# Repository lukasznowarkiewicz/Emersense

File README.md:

# Emersense - Emergency Vehicle Detection System

## Introduction

Emersense is an innovative project developed by a group of dedicated students from Poznan University of Technology. Initiated during the challenging times of the pandemic, this project was brought to life entirely remotely by a team of four members located in four different cities across Poland. The project was realized as part of a competition organized by Enactus Poland, within the framework of the Enactus student organization, which promotes socially responsible projects.

The primary issue that Emersense aims to address is the often too-late response to an approaching emergency vehicle. This problem poses a significant risk not only to the efficiency of emergency services but also to the safety of both the emergency responders and the general public. By leveraging advanced technology, Emersense seeks to provide a timely warning about approaching emergency vehicles, thereby improving response times and reducing the potential for accidents.

## Solution Overview

The core of the Emersense project is a device that uses microphone data to detect emergency vehicle sirens amidst urban noise. It distinguishes these sirens from other sounds such as street noise and engine sounds, and informs the driver of their presence.

- **Siren Detection:** Utilizes signal processing to identify emergency vehicle sirens.
- **Driver Alert:** Notifies the driver through auditory and visual signals.

## Initial Trials on a PC

At the start, we gathered lots of different siren sounds from the internet to build a sound database for Emersense. We quickly found out there's a huge variety of siren sounds. These sounds not only change from one emergency vehicle to another but also differ a lot between countries. There wasn’t even a standard for sirens within the EU. Despite these challenges, we began with the easiest siren sounds to recognize: the sweep and two-tone sirens.

Our first try at figuring out the siren sounds used the FFT (Fast Fourier Transform) library on a computer with an 8-core Intel Core i7 processor. But, we soon realized it was too complex to process the sounds in real time on this setup. So, we switched to the DFT (Discrete Fourier Transform), which was faster and allowed us to make our first successful programs that could recognize two-tone sirens.

Knowing we couldn’t use Python code directly on a microcontroller for the final product, we started to look into low-power hardware that could work for the Emersense device. This was a big step because it helped us focus on finding a solution that could actually be built into a real, working device.

## Trials on the DevKit

After our initial success, we started writing similar code in C for the ESP32 microcontroller. Our first goal was to get a correct spectrum of the signal received from the microphone. 

We soon realized that an electret microphone with an operational amplifier connected to an analog input was giving very inconsistent results. After trying out three more microphone modules, which all produced similarly poor outcomes, we switched to a MEMS microphone that uses the I2S bus - the INMP441. 

Eventually, we managed to get preliminarily satisfying results and programmed it to recognize one type of two-tone siren.

https://github.com/lukasznowarkiewicz/Emersense/assets/82212257/3abe5127-96e8-427c-9536-c156f4cf9e74

## Device on a Custom PCB

As the project evolved, it became necessary for the device not only to function efficiently but also to have an appealing marketing appearance. This required moving away from the mess of wires on breadboards and prototype boards and towards giving the device a sensible shape on a custom PCB, along with a fitting enclosure.

### PCB Design

- **Software:** The PCB was designed in KiCad 5.
- **Components:**
  - **ESP32 Module:** Core processing unit.
  - **CP2102N:** For USB connectivity, allowing programming and data reading through the console.
  - **XL1509:** A converter for stepping down from 5V to 3.3V.
  - **SI4713 FM Transmitter with RDS:** We planned to generate an 'Traffic' RDS signal, which could switch nearby car radios to a traffic channel to broadcast information about the approaching emergency vehicle.
  - **MPU-6050:** For activating energy-saving mode when the vehicle is stationary for an extended period.
  - **INMP441 Digital Microphone and a Legacy Electret Microphone with Amplifier:** To test if the PCB, without the mess of wires, would collect fewer interferences.
  - **SPI 1.3 inch LCD Display (240x240 pixels) with ST7789s Controller.**
- **Shape and Assembly:** The PCB was designed in a round form to accommodate two versions of the device. It was ordered from JLCPCB, with parts from LCSC and manually assembled using a hand-operated pick and place machine.

https://github.com/lukasznowarkiewicz/Emersense/assets/82212257/2ed6d327-44b5-4cf7-a69e-9ff8332732e1

### Enclosure Design

- **Software:** Designed in Fusion 360.
- **Versions:** Two variants were created - one to be mounted on the windshield and another to be inserted into the cigarette lighter socket.
- **Manufacturing:** The enclosures were printed on an Anycubic Photon S SLA printer and cured under a UV nail lamp for hardening.

This stage marked a significant advancement towards finalizing the product, focusing on both functionality and aesthetics.

## Testing and Further Work

This phase was particularly challenging. We were focused on improving the software, but progress was slow. Even with relatively simple sirens, it was difficult to balance the system's sensitivity to quickly detect sirens without being triggered by random noises. More accurate methods, like the autocorrelation function between the spectrum of a reference signal and the captured signal, were computationally complex, and we couldn't implement them to work in real-time.

At the same time, the competition, which emphasized presenting the project rather than its operational success, demanded a significant amount of time for preparing presentations and other materials. This took away valuable time that could have been spent on development. Moreover, a complete misunderstanding of the problem we were working on and what it takes to work on such projects by the leadership of the student organization didn't make things easier.

https://github.com/lukasznowarkiewicz/Emersense/assets/82212257/557e5657-ebb7-40b5-8d4b-21e4bb15feb9

Considering all these challenges, after presenting our project at the competition, we decided to close the project. Interestingly, after we had stopped working on it, the rector of the Poznan University of Technology showed interest in the device, having heard about it in local TV news. He wanted to assemble a team of doctors and PhD students to assist in the project. However, by that time, we had already concluded the project, seeing no further prospects for it. This experience was a valuable lesson on how institutions like universities can sometimes fall short in supporting such projects.

## Summary - Conclusions

Reflecting on the Emersense project, we came away with several crucial insights. A major gap in our approach was the lack of a clear business model, an oversight that might have been mitigated by considering the device as part of a larger integrated system. The complexity of distinguishing emergency vehicle sirens—a problem we initially underestimated—proved to be a significant challenge. Our discussions with industry professionals, including a director from a leading automotive computer company, highlighted the universal struggle with this issue. Their interest in collaboration pointed to its relevance, yet the continued absence of such technology in cars indicates a widespread challenge.

Market demand for the device remained uncertain, raising questions about its commercial viability. Although integrating the technology with a charger offered a potential pathway, the standalone module concept failed to meet expectations. This was a lesson in both the technological hurdles and the importance of clear value propositions in product design.

A critical shortcoming in our development process was the organization of software work, particularly the lack of emphasis on automated testing. Effective development practices should have prioritized automated tests for every software version, introducing additional complexities such as hardware simulation and the input of audio in the I2S format. This approach would not only have streamlined troubleshooting but also ensured more rigorous validation of our system's performance.

The project's discontinuation, while disheartening, provided invaluable lessons on navigating the intricate balance between technical innovation and commercial strategy in the automotive technology space.

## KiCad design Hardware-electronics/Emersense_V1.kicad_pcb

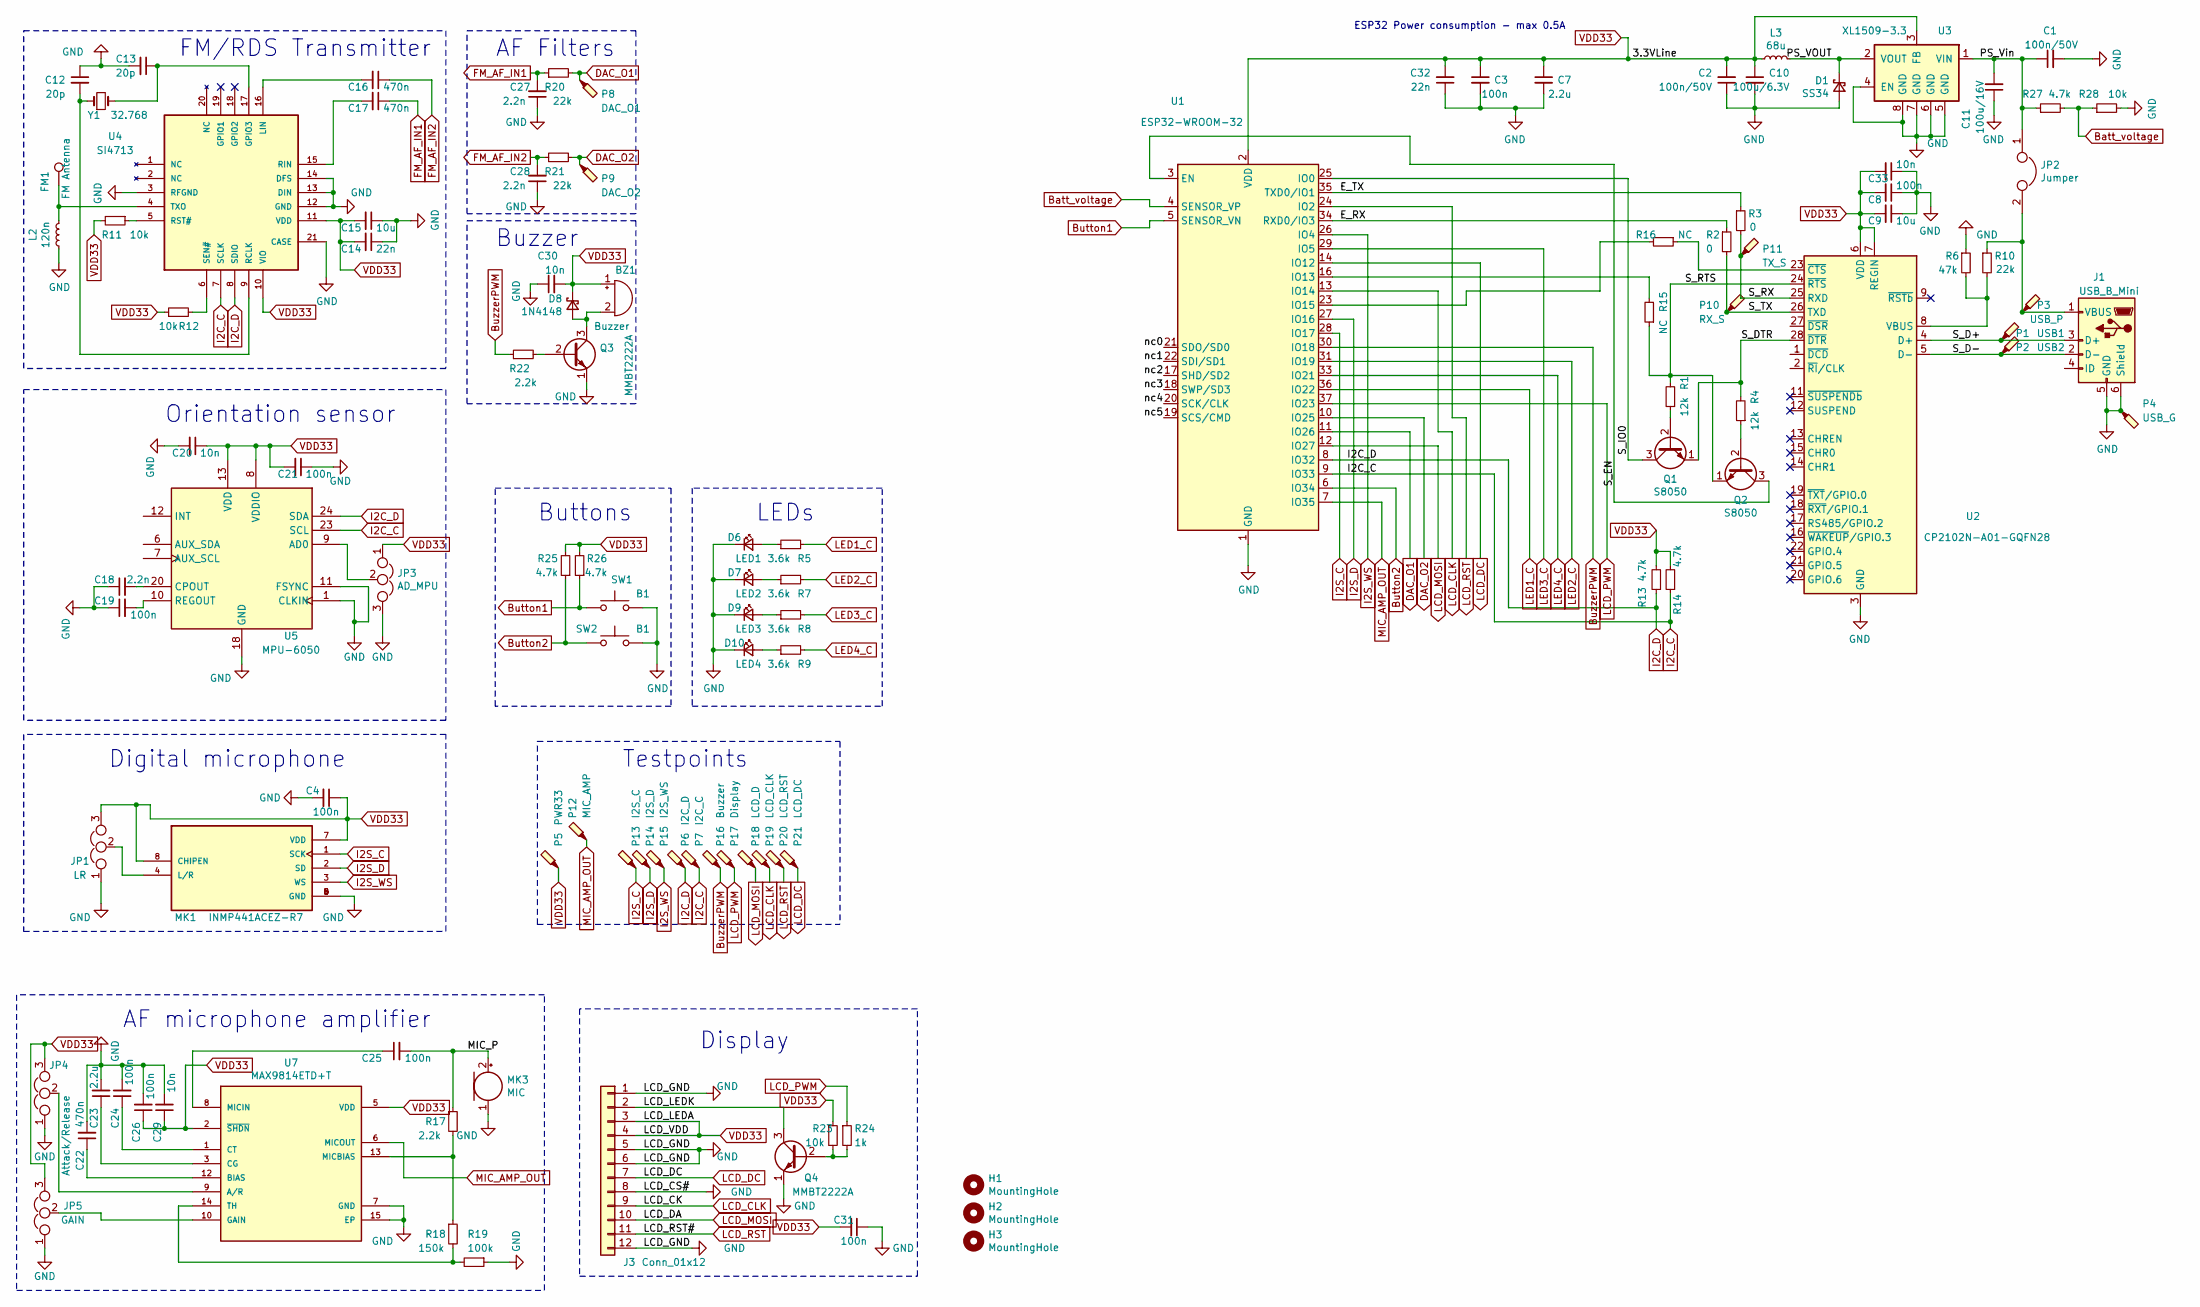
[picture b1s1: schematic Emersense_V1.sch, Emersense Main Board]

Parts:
BZ1: Buzzer; MLT-5030
C1, C2: 100n/50V; C_0805_2012Metric; Voltage 50V
C3, C4, C8, C19, C21, C31: 100n; C_0402_1005Metric
C7, C23: 2.2u; C_0603_1608Metric
C9: 10u; C_0805_2012Metric
C10: 100u/6.3V; C_1210_3225Metric; Voltage 6.3V
C11: 100u/16V; C_1210_3225Metric; Voltage 16V
C12, C13: 20p; C_0402_1005Metric; Voltage 50V
C14, C32: 22n; C_0402_1005Metric
C15: 10u; C_0603_1608Metric
C16, C17, C22: 470n; C_0603_1608Metric; Voltage 10V
C18: 2.2n; C_0603_1608Metric; Voltage 50V
C20, C30: 10n; C_0402_1005Metric; Voltage 50V
C24, C25, C26: 100n; C_0603_1608Metric; Voltage 50V
C27, C28: 2.2n; C_0402_1005Metric; Voltage 50V
C29: 10n; C_0603_1608Metric; Voltage 50V
C33: 10n; C_0805_2012Metric; Voltage 50V
D1: SS34; SOD-123FL
D6: LED1; D_0402_1005Metric
D7: LED2; D_0402_1005Metric
D8: 1N4148; D_SOD-523
D9: LED3; D_0402_1005Metric
D10: LED4; D_0402_1005Metric
FM1: FM Antenna; TestPoint_THTPad_1.0x1.0mm_Drill0.5mm
H1, H2, H3: MountingHole; M1_screw
J1: USB_B_Mini; U-M-M5DS-W-4
J3: Conn_01x12; SCREEN_Footprint_extended
JP1: LR; 3_jumper_1
JP2: Jumper; SolderJumper-2_P1.3mm_Open_RoundedPad1.0x1.5mm
JP3: AD_MPU; 3_jumper_1
JP4: Attack/Release; 3_jumper_1
JP5: GAIN; 3_jumper_1
L2: 120n; L_0402_1005Metric
L3: 68u; SWPA5040S680MT
MK1: INMP441ACEZ-R7; MIC_INMP441ACEZ-R7; PARTREV 1.1
MK3: MIC; B4013AM423-093
P1: USB1; TestPoint_Pad_D1.0mm
P2: USB2; TestPoint_Pad_D1.0mm
P3: USB_P; TestPoint_Pad_D1.0mm
P4: USB_G; TestPoint_Pad_D1.0mm
P5: PWR33; TestPoint_Pad_D1.0mm
P6: I2C_D; TestPoint_Pad_D1.0mm
P7: I2C_C; TestPoint_Pad_D1.0mm
P8: DAC_O1; TestPoint_Pad_D1.0mm
P9: DAC_O2; TestPoint_Pad_D1.0mm
P10: RX_S; TestPoint_Pad_D1.0mm
P11: TX_S; TestPoint_Pad_D1.0mm
P12: MIC_AMP; TestPoint_Pad_D1.0mm
P13: I2S_C; TestPoint_Pad_D1.0mm
P14: I2S_D; TestPoint_Pad_D1.0mm
P15: I2S_WS; TestPoint_Pad_D1.0mm
P16: Buzzer; TestPoint_Pad_D1.0mm
P17: Display; TestPoint_Pad_D1.0mm
P18: LCD_D; TestPoint_Pad_D1.0mm
P19: LCD_CLK; TestPoint_Pad_D1.0mm
P20: LCD_RST; TestPoint_Pad_D1.0mm
P21: LCD_DC; TestPoint_Pad_D1.0mm
Q1, Q2: S8050; SOT-23-R
Q3, Q4: MMBT2222A; SOT-23-R
R1, R4: 12k; R_0402_1005Metric
R2, R3: 0; R_0402_1005Metric
R5, R7, R8, R9: 3.6k; R_0402_1005Metric
R6: 47k; R_0402_1005Metric
R10, R20, R21: 22k; R_0402_1005Metric
R11, R12, R23, R28: 10k; R_0402_1005Metric
R13, R14, R25, R26, R27: 4.7k; R_0402_1005Metric
R15, R16: NC; R_0402_1005Metric
R17, R22: 2.2k; R_0402_1005Metric
R18: 150k; R_0402_1005Metric
R19: 100k; R_0402_1005Metric
R24: 1k; R_0402_1005Metric
SW1, SW2: B1; TS-1086E
U1: ESP32-WROOM-32
U2: CP2102N-A01-GQFN28; QFN-28-1EP_5x5mm_P0.5mm_EP3.35x3.35mm
U3: XL1509-3.3; SOP-8_3.76x4.96mm_P1.27mm
U4: SI4713; QFN50P300X300X60-21N
U5: MPU-6050; InvenSense_QFN-24_4x4mm_P0.5mm
U7: MAX9814ETD+T; DFN-14-1EP_3x3mm_P0.4mm_EP1.78x2.35mm; PARTREV 3
Y1: 32.768; Crystal_SMD_G8-2Pin_3.2x1.5mm

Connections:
/E_RX: R2.1, U1.34 (RXD0/IO3)
/E_TX: R3.1, U1.35 (TXD0/IO1)
/LCD_LEDK: J3.2, Q4.3 (C)
/MIC_P: C25.2, MK3.2 (+), R17.1
/PS_VOUT: D1.1 (K), L3.1, U3.2 (VOUT)
/PS_Vin: C1.1, C11.2, JP2.1, R27.1, U3.1 (VIN)
/S_D+: J1.3 (D+), P1.1, U2.4 (D+)
/S_D-: J1.2 (D-), P2.1, U2.5 (D-)
/S_DTR: Q1.1 (E), R4.2, U2.28 (~DTR)
/S_EN: Q2.3 (C), U1.3 (EN)
/S_IO0: Q1.3 (C), U1.25 (IO0)
/S_RTS: Q2.1 (E), R1.2, R15.1, U2.24 (~RTS)
/S_RX: P11.1, R3.2, U2.25 (RXD)
/S_TX: P10.1, R2.2, U2.26 (TXD)
/nc0: U1.21 (SDO/SD0)
/nc1: U1.22 (SDI/SD1)
/nc2: U1.17 (SHD/SD2)
/nc3: U1.18 (SWP/SD3)
/nc4: U1.20 (SCK/CLK)
/nc5: U1.19 (SCS/CMD)
Batt_voltage: R27.2, R28.1, U1.4 (SENSOR_VP)
Button1: R26.1, SW1.1, U1.5 (SENSOR_VN)
Button2: R25.1, SW2.1, U1.6 (IO34)
BuzzerPWM: P16.1, R22.1, U1.30 (IO18)
DAC_O1: P8.1, R20.2, U1.11 (IO26)
DAC_O2: P9.1, R21.2, U1.10 (IO25)
FM_AF_IN1: C17.1, C27.2, R20.1
FM_AF_IN2: C16.1, C28.2, R21.1
GND: C1.2, C2.1, C3.2, C4.2, C7.2, C8.1, C9.1, C10.2, C11.1, C12.1, C13.2, C14.1, C15.1, C18.1, C19.1, C20.2, C21.1, C22.2, C23.2, C24.2, C26.2, C27.1, C28.1, C29.2, C30.1, C31.1, C32.1, C33.1, D1.2 (A), D6.1 (K), D7.1 (K), D9.1 (K), D10.1 (K), J1.5 (GND), J1.6 (Shield), J3.1, J3.5, J3.6, J3.8, J3.12, JP1.1, JP3.3, JP4.1, JP5.1, L2.2, MK1.5 (GND), MK1.6 (GND), MK1.9 (GND), MK3.1 (-), P4.1, Q3.1 (E), Q4.1 (E), R6.1, R19.1, R28.2, SW1.2, SW2.2, U1.1 (GND), U1.15 (GND), U1.38 (GND), U1.39 (GND), U2.3 (GND), U2.29 (GND), U3.4 (EN), U3.5 (GND), U3.6 (GND), U3.7 (GND), U3.8 (GND), U4.3 (RFGND), U4.12 (GND), U4.13 (DIN), U4.14 (DFS), U4.21 (CASE), U5.1 (CLKIN), U5.11 (FSYNC), U5.18 (GND), U7.7 (GND), U7.15 (EP)
I2C_C: P7.1, R14.1, U1.9 (IO33), U4.7 (SCLK), U5.23 (SCL)
I2C_D: P6.1, R13.1, U1.8 (IO32), U4.8 (SDIO), U5.24 (SDA)
I2S_C: MK1.1 (SCK), P13.1, U1.28 (IO17)
I2S_D: MK1.2 (SD), P14.1, U1.27 (IO16)
I2S_WS: MK1.3 (WS), P15.1, U1.26 (IO4)
LCD_CLK: J3.9, P19.1, U1.13 (IO14)
LCD_DC: J3.7, P21.1, U1.14 (IO12)
LCD_MOSI: J3.10, P18.1, U1.12 (IO27)
LCD_PWM: P17.1, R24.1, U1.37 (IO23)
LCD_RST: J3.11, P20.1, U1.24 (IO2)
LED1_C: R5.2, U1.36 (IO22)
LED2_C: R7.2, U1.31 (IO19)
LED3_C: R8.2, U1.29 (IO5)
LED4_C: R9.2, U1.33 (IO21)
MIC_AMP_OUT: P12.1, U1.7 (IO35), U7.6 (MICOUT)
unnamed: BZ1.2 (+), D8.2 (A), Q3.3 (C)
unnamed: C12.2, U4.9 (RCLK), Y1.1
unnamed: C13.1, U4.17 (GPIO3), Y1.2
unnamed: C16.2, U4.16 (LIN)
unnamed: C17.2, U4.15 (RIN)
unnamed: C18.2, U5.20 (CPOUT)
unnamed: C19.2, U5.10 (REGOUT)
unnamed: C22.1, U7.12 (BIAS)
unnamed: C23.1, U7.3 (CG)
unnamed: C24.1, U7.1 (CT)
unnamed: C25.1, U7.8 (MICIN)
unnamed: D6.2 (A), R5.1
unnamed: D7.2 (A), R7.1
unnamed: D9.2 (A), R8.1
unnamed: D10.2 (A), R9.1
unnamed: FM1.1, L2.1, U4.4 (TXO)
unnamed: J1.1 (VBUS), JP2.2, P3.1, R10.1
unnamed: JP1.2, MK1.4 (L/R)
unnamed: JP3.2, U5.9 (AD0)
unnamed: JP4.2, U7.9 (A/R)
unnamed: JP5.2, U7.10 (GAIN)
unnamed: Q1.2 (B), R1.1
unnamed: Q2.2 (B), R4.1
unnamed: Q3.2 (B), R22.2
unnamed: Q4.2 (B), R23.2, R24.2
unnamed: R6.2, R10.2, U2.8 (VBUS)
unnamed: R11.1, U4.5 (RST#)
unnamed: R12.2, U4.6 (SEN#)
unnamed: R15.2, U1.16 (IO13)
unnamed: R16.1, U2.23 (~CTS)
unnamed: R16.2, U1.23 (IO15)
unnamed: R17.2, R18.1, U7.13 (MICBIAS)
unnamed: R18.2, R19.2, U7.14 (TH)
VDD33: BZ1.1 (-), C2.2, C3.1, C4.1, C7.1, C8.2, C9.2, C10.1, C14.2, C15.2, C20.1, C21.2, C26.1, C29.1, C30.2, C31.2, C32.2, C33.2, D8.1 (K), J3.3, J3.4, JP1.3, JP3.1, JP4.3, JP5.3, L3.2, MK1.7 (VDD), MK1.8 (CHIPEN), P5.1, R11.2, R12.1, R13.2, R14.2, R23.1, R25.2, R26.2, U1.2 (VDD), U2.6 (VDD), U2.7 (REGIN), U3.3 (FB), U4.10 (VIO), U4.11 (VDD), U5.8 (VDDIO), U5.13 (VDD), U7.2 (~SHDN), U7.5 (VDD)

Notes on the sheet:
ESP32 Power consumption - max 0.5A
AF Filters
FM/RDS Transmitter
Buzzer
Testpoints
Orientation sensor
Digital microphone
AF microphone amplifier
Display
LEDs
Buttons

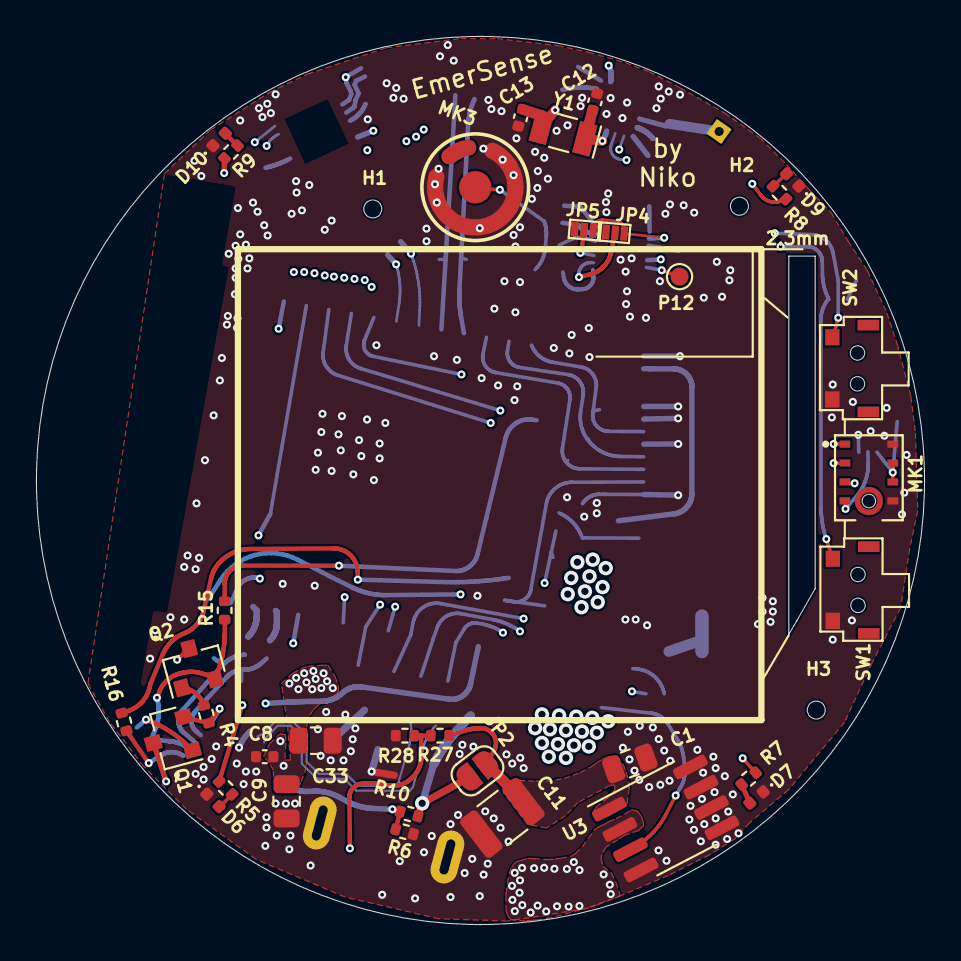
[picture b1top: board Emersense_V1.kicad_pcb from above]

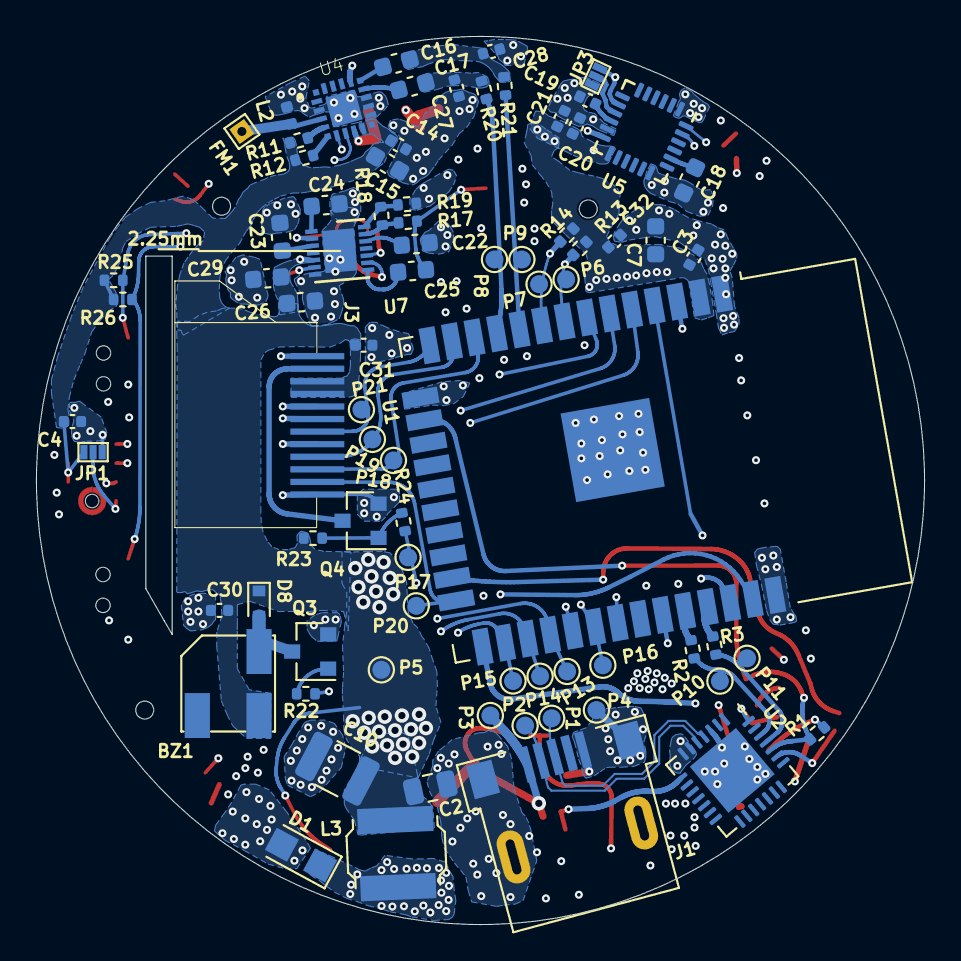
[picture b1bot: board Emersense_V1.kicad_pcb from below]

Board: 4 copper layers, 49.3 x 49.3 mm, 115 parts (78 on the bottom side), 72 nets.

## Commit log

2024-04-01 Added hardware-electronics
2024-04-01 Added hardware-mechanical
2024-04-04 Update README.md - added images and videos
2024-04-04 Added images and videos
2024-04-04 Cropped logo
